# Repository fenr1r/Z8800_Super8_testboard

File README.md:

# Z8800_Super8_testboard

Test board for MCU Z08800020 (Super8 / Z8) from Zilog.

More details : plz refer my blog [https://vita-brevis.hatenablog.com/archive/category/Z8800%20%28Super8%29].

## bugs

**These bugs are currently NOT fixed yet**. Be careful for using assets.

- No need for implementing pull-up register arrays RN2. Instead of this, you HAVE TO ADD pull-down register to A13-A15
- Port 2 signals are wrongly connected to DAC08. The bits order are backwards. B0 SHOULD be connected to P2_7, B7 SHOULD be connected to P2_0.
- The pin assigns of DTR and RxD on the D-sub connector are backwards.
- GAL logic comment SHOULD BE FIXED as : #RAM_WE = #DS # R/#W, #RAM_OE = #DS # !R/#W

These are not bugs but recommended to be fixed:

- Add #DM (P3_5) signal to GAL input. #DM is a signal to distinguish between access to the program memory and to the data memory.

## Spec

- ROM 27256 (32kB)
- RAM 62256 (32kB)
- Address decoder GAL16V8B
- 1 LED port (LED x8)
- 1 DAC port (DAC08 ... to accomplish the sine wave generation described on Super8 Application Note)
- 1 UART port (RS-232)

## Assets

### Schematics

KiCad v9

[KiCad_Z8800](KiCad_Z8800/KiCad_Z8800_sch.pdf)

### PCB design

KiCad v9

### GAL JEDEC file

WinCupl

### Program

Macro Asseembler

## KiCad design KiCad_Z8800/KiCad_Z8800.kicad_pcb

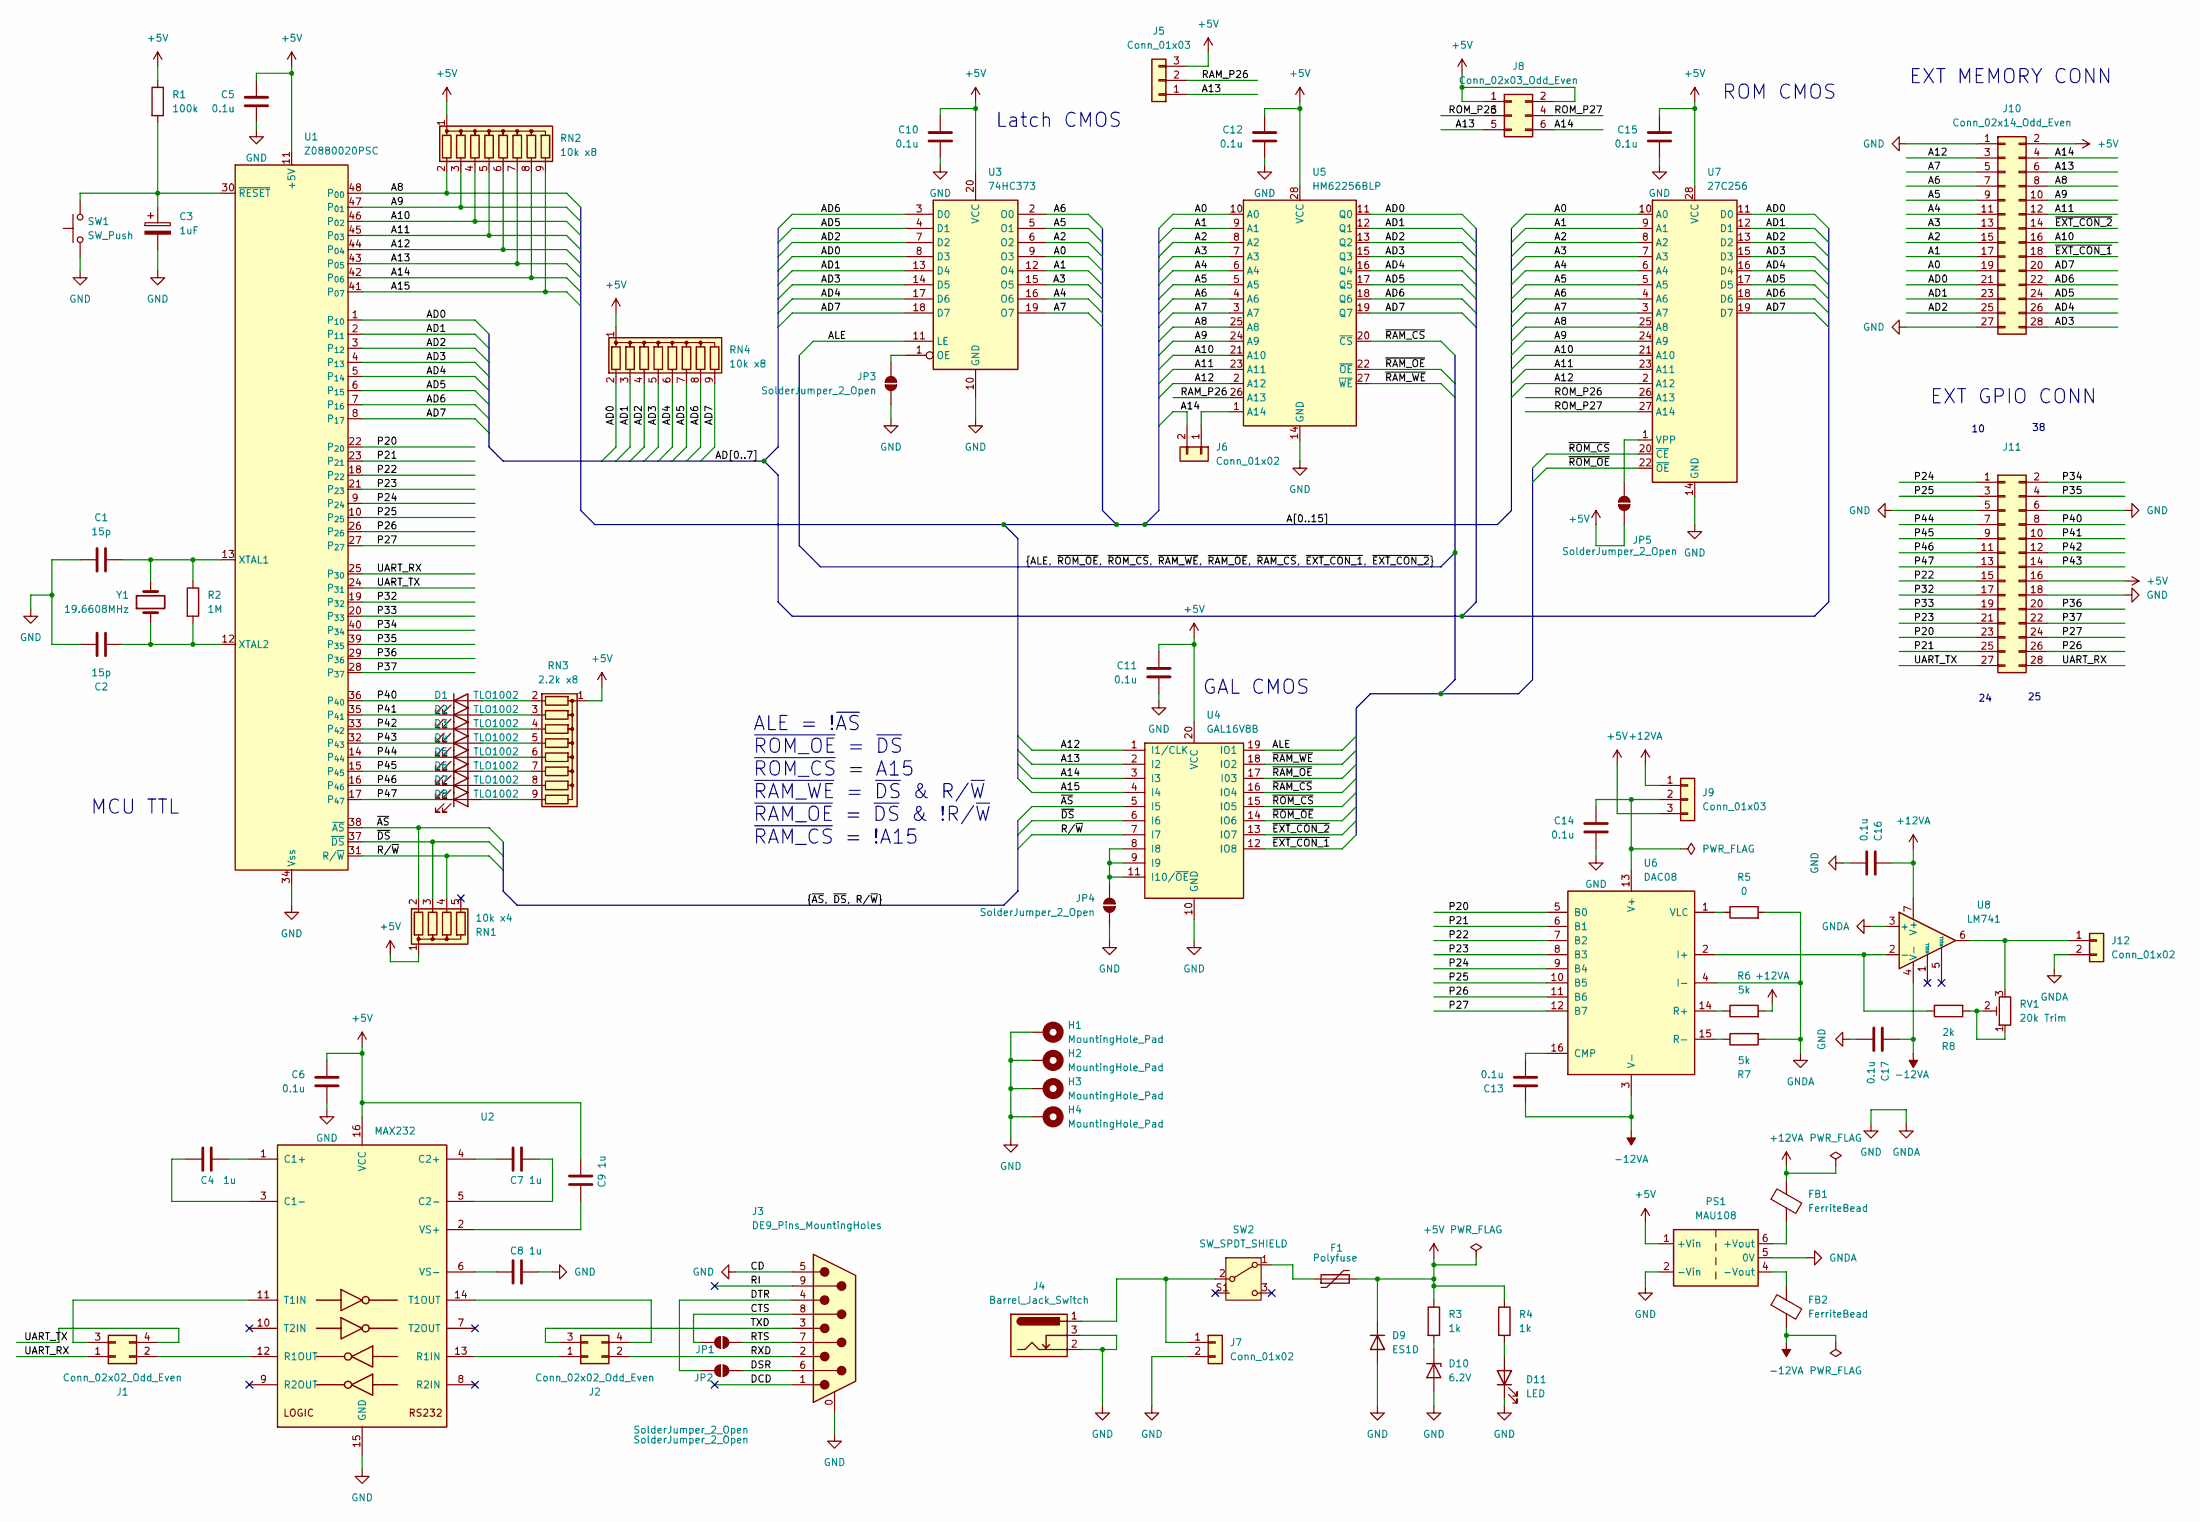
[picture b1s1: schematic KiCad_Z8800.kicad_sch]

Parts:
C1, C2: 15p; C_1206_3216Metric_Pad1.33x1.80mm_HandSolder
C3: 1uF; CP_Radial_D6.3mm_P2.50mm
C4, C7, C8, C9: 1u; C_0603_1608Metric_Pad1.08x0.95mm_HandSolder
C5, C10, C15, C16, C17: 0.1u; C_0603_1608Metric_Pad1.08x0.95mm_HandSolder
C6, C11, C12, C13, C14: 0.1u; C_Disc_D4.7mm_W2.5mm_P5.00mm
D1, D2, D3, D4, D5, D6, D7, D8: TLO1002; LED_0805_2012Metric_Pad1.15x1.40mm_HandSolder
D9: ES1D; D_SMA_Handsoldering
D10: 6.2V; D_DO-35_SOD27_P2.54mm_Vertical_KathodeUp
D11: LED; LED_D3.0mm
F1: Polyfuse; C_Disc_D8.0mm_W2.5mm_P5.00mm
FB1, FB2: FerriteBead; L_0603_1608Metric_Pad1.05x0.95mm_HandSolder
H1, H2, H3, H4: MountingHole_Pad; MountingHole_3.2mm_M3_Pad
J1, J2: Conn_02x02_Odd_Even; PinHeader_2x02_P2.54mm_Vertical
J3: DE9_Pins_MountingHoles; DSUB-9_Pins_Horizontal_P2.77x2.84mm_EdgePinOffset4.94mm_Hou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
J4: Barrel_Jack_Switch; BarrelJack_Horizontal
J5, J9: Conn_01x03; PinHeader_1x03_P2.54mm_Vertical
J6: Conn_01x02; PinHeader_1x02_P2.54mm_Vertical
J7, J12: Conn_01x02; JST_XH_B2B-XH-A_1x02_P2.50mm_Vertical
J8: Conn_02x03_Odd_Even; PinHeader_2x03_P2.54mm_Vertical
J10, J11: Conn_02x14_Odd_Even; PinHeader_2x14_P2.54mm_Vertical
JP1, JP2, JP3, JP4, JP5: SolderJumper_2_Open; SolderJumper-2_P1.3mm_Open_RoundedPad1.0x1.5mm
PS1: MAU108; Converter_DCDC_XP_POWER-IAxxxxS_THT
R1: 100k; R_Axial_DIN0207_L6.3mm_D2.5mm_P7.62mm_Horizontal
R2: 1M; R_0603_1608Metric_Pad0.98x0.95mm_HandSolder
R3, R4: 1k; R_Axial_DIN0207_L6.3mm_D2.5mm_P7.62mm_Horizontal
R5: 0; R_0603_1608Metric_Pad0.98x0.95mm_HandSolder
R6, R7: 5k; R_Axial_DIN0207_L6.3mm_D2.5mm_P7.62mm_Horizontal
R8: 2k; R_Axial_DIN0207_L6.3mm_D2.5mm_P7.62mm_Horizontal
RN1: 10k x4; R_Array_SIP5
RN2, RN4: 10k x8; R_Array_SIP9
RN3: 2.2k x8; R_Array_SIP9
RV1: 20k Trim; Potentiometer_Runtron_RM-065_Vertical
SW1: SW_Push; SW_PUSH_6mm
SW2: SW_SPDT_SHIELD; SW_2MS1-T1-B4-VS2-Q-E-S
U1: Z0880020PSC; DIP-48_W15.24mm_Socket_LongPads
U2: MAX232; DIP-16_W7.62mm_Socket_LongPads
U3: 74HC373; DIP-20_W7.62mm_Socket_LongPads
U4: GAL16V8B; DIP-20_W7.62mm_Socket_LongPads
U5: HM62256BLP; DIP-28_W15.24mm
U6: DAC08; DIP-16_W7.62mm_Socket_LongPads
U7: 27C256; DIP_Socket-28_W11.9mm_W12.7mm_W15.24mm_W17.78mm_W18.5mm_3M_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
U8: LM741; DIP-8_W7.62mm_Socket_LongPads
Y1: 19.6608MHz; Crystal_HC49-U_Vertical

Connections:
+5V: C5.1, C6.1, C9.1, C10.1, C11.1, C12.1, C15.1, D9.1 (K), F1.2, J5.3, J8.1, J8.2, J9.3, J10.2, J11.16, JP5.2 (B), PS1.1 (+Vin), R1.1, R3.1, R4.1, RN1.1 (common), RN2.1 (common), RN3.1 (common), RN4.1 (common), U1.11 (+5V), U2.16 (VCC), U3.20 (VCC), U4.20 (VCC), U5.28 (VCC), U7.28 (VCC)
+12VA: C16.1, FB1.1, J9.1, R6.2, U8.7 (V+)
-12VA: C13.1, C17.1, FB2.2, U6.3 (V-), U8.4 (V-)
/A0: J10.19, U3.9 (O3), U5.10 (A0), U7.10 (A0)
/A1: J10.17, U3.12 (O4), U5.9 (A1), U7.9 (A1)
/A2: J10.15, U3.6 (O2), U5.8 (A2), U7.8 (A2)
/A3: J10.13, U3.15 (O5), U5.7 (A3), U7.7 (A3)
/A4: J10.11, U3.16 (O6), U5.6 (A4), U7.6 (A4)
/A5: J10.9, U3.5 (O1), U5.5 (A5), U7.5 (A5)
/A6: J10.7, U3.2 (O0), U5.4 (A6), U7.4 (A6)
/A7: J10.5, U3.19 (O7), U5.3 (A7), U7.3 (A7)
/A8: J10.8, RN2.2 (R1), U1.48 (P_{00}), U5.25 (A8), U7.25 (A8)
/A9: J10.10, RN2.3 (R2), U1.47 (P_{01}), U5.24 (A9), U7.24 (A9)
/A10: J10.16, RN2.4 (R3), U1.46 (P_{02}), U5.21 (A10), U7.21 (A10)
/A11: J10.12, RN2.5 (R4), U1.45 (P_{03}), U5.23 (A11), U7.23 (A11)
/A12: J10.3, RN2.6 (R5), U1.44 (P_{04}), U4.1 (I1/CLK), U5.2 (A12), U7.2 (A12)
/A13: J5.1, J8.5, J10.6, RN2.7 (R6), U1.43 (P_{05}), U4.2 (I2)
/A14: J6.2, J8.6, J10.4, RN2.8 (R7), U1.42 (P_{06}), U4.3 (I3)
/A15: RN2.9 (R8), U1.41 (P_{07}), U4.4 (I4)
/AD0: J10.21, RN4.2 (R1), U1.1 (P_{10}), U3.8 (D3), U5.11 (Q0), U7.11 (D0)
/AD1: J10.23, RN4.3 (R2), U1.2 (P_{11}), U3.13 (D4), U5.12 (Q1), U7.12 (D1)
/AD2: J10.25, RN4.4 (R3), U1.3 (P_{12}), U3.7 (D2), U5.13 (Q2), U7.13 (D2)
/AD3: J10.28, RN4.5 (R4), U1.4 (P_{13}), U3.14 (D5), U5.15 (Q3), U7.15 (D3)
/AD4: J10.26, RN4.6 (R5), U1.5 (P_{14}), U3.17 (D6), U5.16 (Q4), U7.16 (D4)
/AD5: J10.24, RN4.7 (R6), U1.6 (P_{15}), U3.4 (D1), U5.17 (Q5), U7.17 (D5)
/AD6: J10.22, RN4.8 (R7), U1.7 (P_{16}), U3.3 (D0), U5.18 (Q6), U7.18 (D6)
/AD7: J10.20, RN4.9 (R8), U1.8 (P_{17}), U3.18 (D7), U5.19 (Q7), U7.19 (D7)
/ALE: U3.11 (LE), U4.19 (IO1)
/CTS: J3.8, JP1.2 (B)
/DCD: J3.1
/DSR: J3.6, JP2.1 (A)
/DTR: J3.4, JP2.2 (B)
/P20: J11.23, U1.22 (P_{20}), U6.5 (B0)
/P21: J11.25, U1.23 (P_{21}), U6.6 (B1)
/P22: J11.15, U1.18 (P_{22}), U6.7 (B2)
/P23: J11.21, U1.21 (P_{23}), U6.8 (B3)
/P24: J11.1, U1.9 (P_{24}), U6.9 (B4)
/P25: J11.3, U1.10 (P_{25}), U6.10 (B5)
/P26: J11.26, U1.26 (P_{26}), U6.11 (B6)
/P27: J11.24, U1.27 (P_{27}), U6.12 (B7)
/P32: J11.17, U1.19 (P_{32})
/P33: J11.19, U1.20 (P_{33})
/P34: J11.2, U1.40 (P_{34})
/P35: J11.4, U1.39 (P_{35})
/P36: J11.20, U1.29 (P_{36})
/P37: J11.22, U1.28 (P_{37})
/P40: D1.1 (K), J11.8, U1.36 (P_{40})
/P41: D2.1 (K), J11.10, U1.35 (P_{41})
/P42: D3.1 (K), J11.12, U1.33 (P_{42})
/P43: D4.1 (K), J11.14, U1.32 (P_{43})
/P44: D5.1 (K), J11.7, U1.14 (P_{44})
/P45: D6.1 (K), J11.9, U1.15 (P_{45})
/P46: D7.1 (K), J11.11, U1.16 (P_{46})
/P47: D8.1 (K), J11.13, U1.17 (P_{47})
/RAM_P26: J5.2, U5.26 (A13)
/RI: J3.9
/ROM_P26: J8.3, U7.26 (A13)
/ROM_P27: J8.4, U7.27 (A14)
/RTS: J3.7, JP1.1 (A)
/RXD: J2.2, J3.2
/R/~W: RN1.4 (R3), U1.31 (R/~W), U4.7 (I7)
/TXD: J2.3, J3.3
/UART_RX: J1.1, J11.28, U1.25 (P_{30})
/UART_TX: J1.4, J11.27, U1.24 (P_{31})
/~AS: RN1.2 (R1), U1.38 (~AS), U4.5 (I5)
/~DS: RN1.3 (R2), U1.37 (~DS), U4.6 (I6)
/~EXT_CON_1: J10.18, U4.12 (IO8)
/~EXT_CON_2: J10.14, U4.13 (IO7)
/~RAM_CS: U4.16 (IO4), U5.20 (~CS)
/~RAM_OE: U4.17 (I03), U5.22 (~OE)
/~RAM_WE: U4.18 (IO2), U5.27 (~WE)
/~ROM_CS: U4.15 (IO5), U7.20 (~CE)
/~ROM_OE: U4.14 (IO6), U7.22 (~OE)
GND: C1.1, C2.1, C3.2, C5.2, C6.2, C8.1, C10.2, C11.2, C12.2, C14.2, C15.2, C16.2, C17.2, D9.2 (A), D10.2 (A), D11.1 (K), H1.1, H2.1, H3.1, H4.1, J3.0 (PAD), J3.5, J4.2, J4.3, J7.2, J10.1, J10.27, J11.5, J11.6, J11.18, J12.2, JP3.1 (A), JP4.1 (A), PS1.2 (-Vin), PS1.5 (0V), R5.2, R7.2, SW1.1, U1.34 (Vss), U2.15 (GND), U3.10 (GND), U4.10 (GND), U5.14 (GND), U6.4 (I-), U7.14 (GND), U8.3 (+)
unnamed: D1.2 (A), RN3.2 (R1)
unnamed: D2.2 (A), RN3.3 (R2)
unnamed: D3.2 (A), RN3.4 (R3)
unnamed: D4.2 (A), RN3.5 (R4)
unnamed: D5.2 (A), RN3.6 (R5)
unnamed: D6.2 (A), RN3.7 (R6)
unnamed: D7.2 (A), RN3.8 (R7)
unnamed: D8.2 (A), RN3.9 (R8)
unnamed: D10.1 (K), R3.2
unnamed: D11.2 (A), R4.2
unnamed: J1.2, U2.12 (R1OUT)
unnamed: J1.3, U2.11 (T1IN)
unnamed: J2.1, U2.13 (R1IN)
unnamed: J2.4, U2.14 (T1OUT)
unnamed: J6.1, U5.1 (A14)
unnamed: J4.1, J7.1, SW2.2 (B)
unnamed: C14.1, J9.2, U6.13 (V+)
unnamed: J12.1, RV1.3, U8.6
unnamed: JP3.2 (B), U3.1 (OE)
unnamed: JP4.2 (B), U4.8 (I8), U4.9 (I9), U4.11 (I10/~OE)
unnamed: JP5.1 (A), U7.1 (VPP)
unnamed: FB1.2, PS1.6 (+Vout)
unnamed: FB2.1, PS1.4 (-Vout)
unnamed: R8.2, RV1.1, RV1.2
unnamed: F1.1, SW2.1 (A)
unnamed: C1.2, R2.1, U1.13 (XTAL1), Y1.2
unnamed: C2.2, R2.2, U1.12 (XTAL2), Y1.1
unnamed: C3.1, R1.2, SW1.2, U1.30 (~RESET)
unnamed: C4.2, U2.1 (C1+)
unnamed: C4.1, U2.3 (C1-)
unnamed: C7.2, U2.4 (C2+)
unnamed: C7.1, U2.5 (C2-)
unnamed: C9.2, U2.2 (VS+)
unnamed: C8.2, U2.6 (VS-)
unnamed: C13.2, U6.16 (CMP)
unnamed: R8.1, U6.2 (I+), U8.2 (-)
unnamed: R6.1, U6.14 (R+)
unnamed: R7.1, U6.15 (R-)
unnamed: R5.1, U6.1 (VLC)

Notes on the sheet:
GAL CMOS
EXT GPIO CONN
Latch CMOS
ALE = !~{AS} ~{ROM_OE} = ~{DS} ~{ROM_CS} = A15 ~{RAM_WE} = ~{DS} & R/~{W} ~{RAM_OE} = ~{DS} & !R/~{W} ~{RAM_CS} = !A15
ROM CMOS
MCU TTL
EXT MEMORY CONN

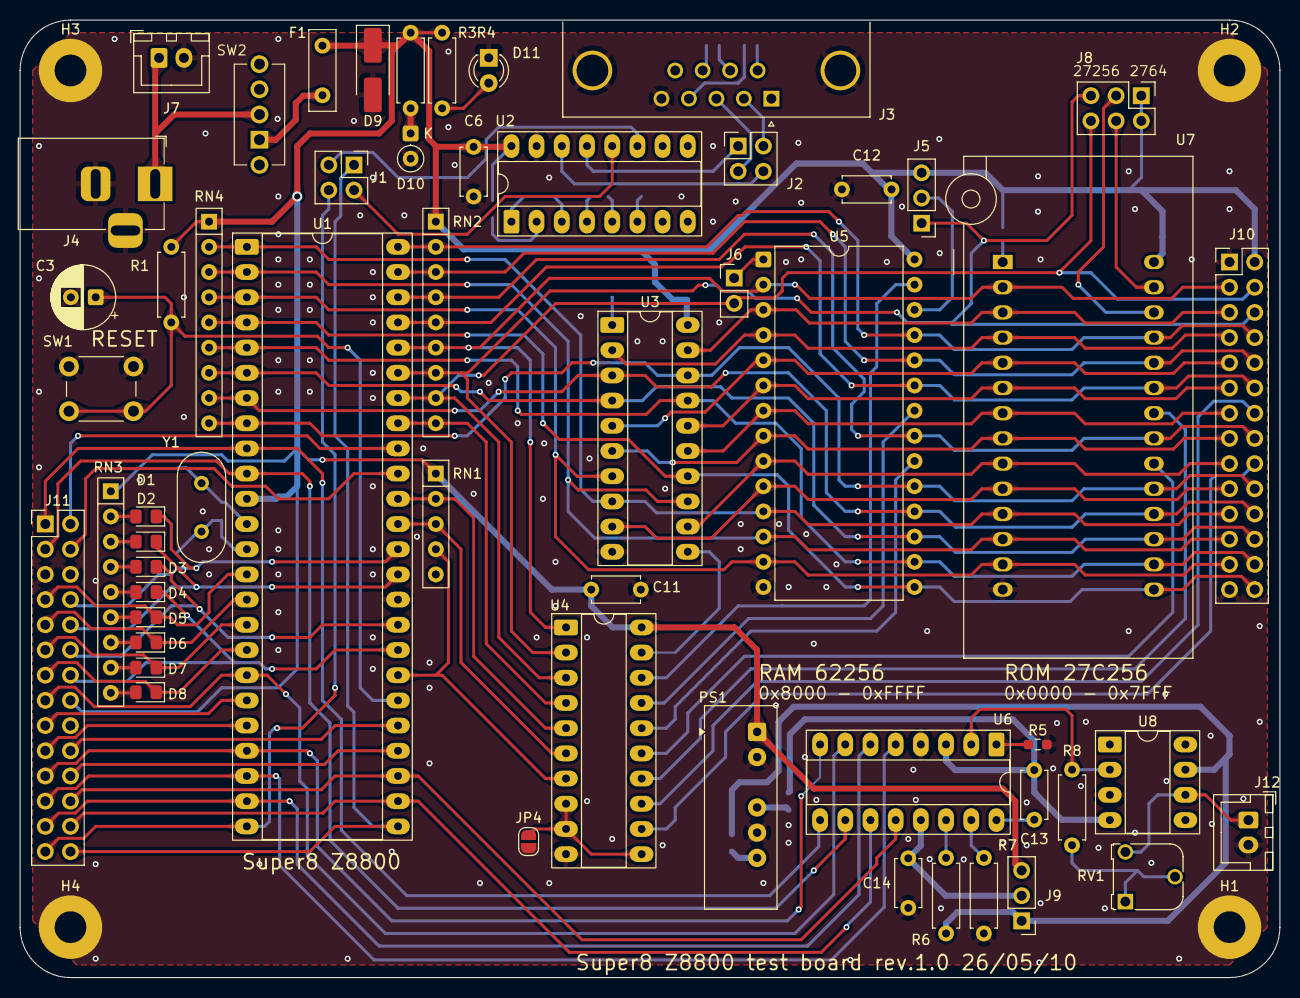
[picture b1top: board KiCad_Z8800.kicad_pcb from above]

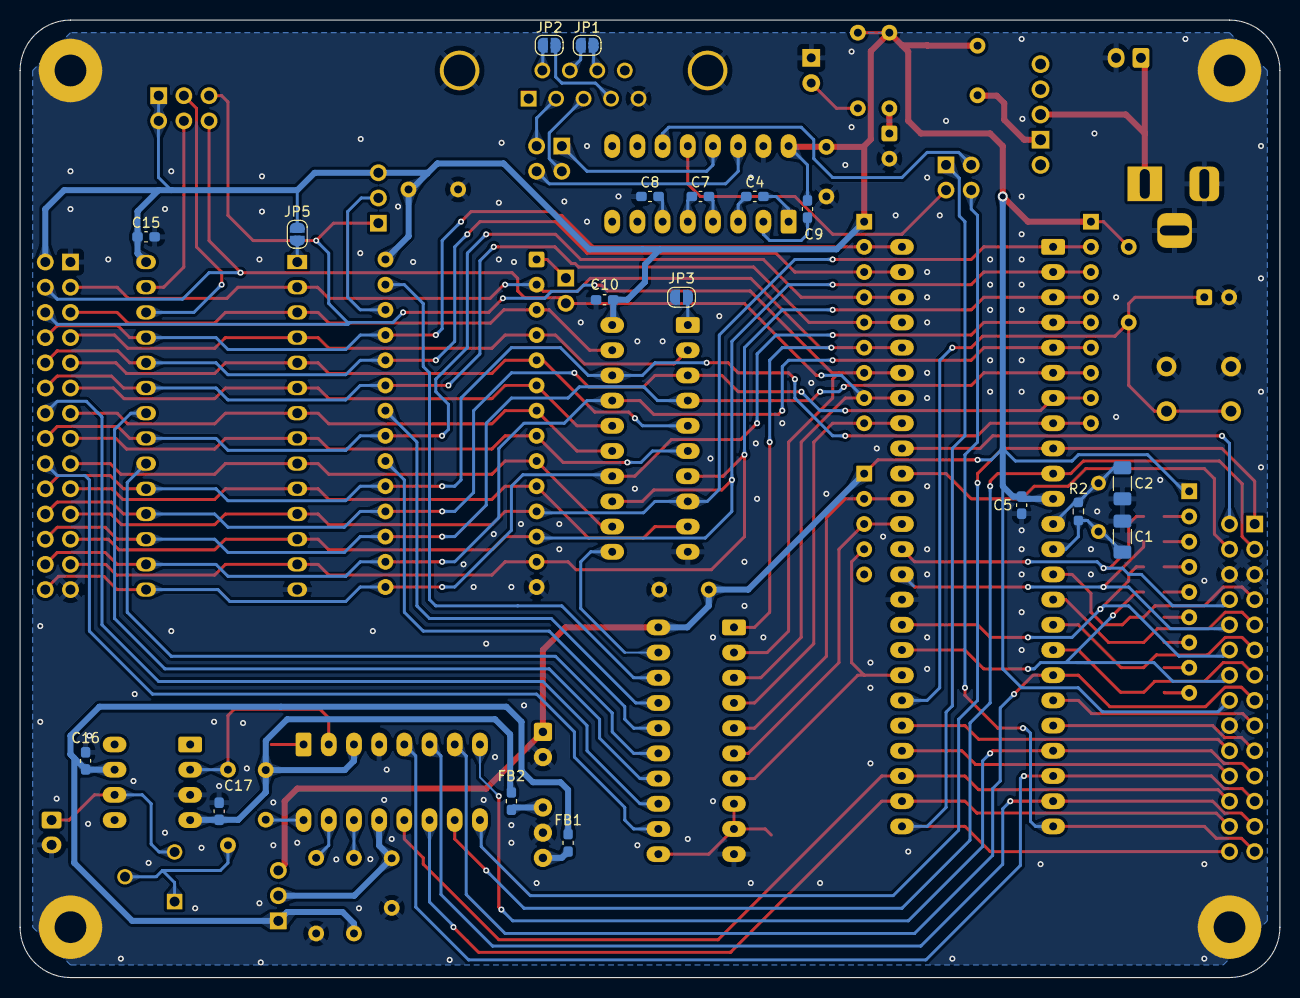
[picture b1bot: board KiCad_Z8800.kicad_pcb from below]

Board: 2 copper layers, 127.0 x 96.5 mm, 77 parts (18 on the bottom side), 111 nets.

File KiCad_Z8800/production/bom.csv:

Designator,Footprint,Quantity,Value,LCSC Part #
"C1, C2",1206,2,15p,
"C10, C15, C16, C17, C5",0603,5,0.1u,
"C11, C12, C13, C14, C6",C_Disc_D4.7mm_W2.5mm_P5.00mm,5,0.1u,
C3,CP_Radial_D6.3mm_P2.50mm,1,1uF,
"C4, C7, C8, C9",0603,4,1u,
"D1, D2, D3, D4, D5, D6, D7, D8",0805,8,TLO1002,
D10,D_DO-35_SOD27_P2.54mm_Vertical_KathodeUp,1,6.2V,
D11,LED_D3.0mm,1,LED,
D9,D_SMA_Handsoldering,1,D,
F1,C_Disc_D8.0mm_W2.5mm_P5.00mm,1,Polyfuse,
"FB1, FB2",0603,2,FerriteBead,
"J1, J2",PinHeader_2x02_P2.54mm_Vertical,2,Conn_02x02_Odd_Even,
"J10, J11",PinHeader_2x14_P2.54mm_Vertical,2,Conn_02x14_Odd_Even,
"J12, J7",JST_XH_B2B-XH-A_1x02_P2.50mm_Vertical,2,Conn_01x02,
J3,DSUB-9_Pins_Horizontal_P2.77x2.84mm_EdgePinOffset4.94mm_Housed_MountingHolesOffset4.94mm,1,DE9_Pins_MountingHoles,
J4,BarrelJack_Horizontal,1,Barrel_Jack_Switch,
"J5, J9",PinHeader_1x03_P2.54mm_Vertical,2,Conn_01x03,
J6,PinHeader_1x02_P2.54mm_Vertical,1,Conn_01x02,
J8,PinHeader_2x03_P2.54mm_Vertical,1,Conn_02x03_Odd_Even,
PS1,Converter_DCDC_XP_POWER-IAxxxxS_THT,1,MAU108,
R1,R_Axial_DIN0207_L6.3mm_D2.5mm_P7.62mm_Horizontal,1,100k,
R2,0603,1,1M,
"R3, R4",R_Axial_DIN0207_L6.3mm_D2.5mm_P7.62mm_Horizontal,2,1k,
R5,0603,1,0,
"R6, R7",R_Axial_DIN0207_L6.3mm_D2.5mm_P7.62mm_Horizontal,2,5k,
R8,R_Axial_DIN0207_L6.3mm_D2.5mm_P7.62mm_Horizontal,1,2k,
RN1,R_Array_SIP5,1,10k x4,
"RN2, RN4",R_Array_SIP9,2,10k x8,
RN3,R_Array_SIP9,1,2.2k x8,
RV1,Potentiometer_Runtron_RM-065_Vertical,1,20k Trim,
SW1,SW_PUSH_6mm,1,SW_Push,
SW2,SW_2MS1-T1-B4-VS2-Q-E-S,1,SW_SPDT_SHIELD,
U1,DIP-48_W15.24mm_Socket_LongPads,1,Z0880020PSC,
U2,DIP-16_W7.62mm_Socket_LongPads,1,MAX232,
U3,DIP-20_W7.62mm_Socket_LongPads,1,74HC373,
U4,DIP-20_W7.62mm_Socket_LongPads,1,GAL16V8B,
U5,DIP-28_W15.24mm,1,HM62256BLP,
U6,DIP-16_W7.62mm_Socket_LongPads,1,DAC08,
U7,DIP_Socket-28_W11.9mm_W12.7mm_W15.24mm_W17.78mm_W18.5mm_3M_228-1277-00-0602J,1,27C256,
U8,DIP-8_W7.62mm_Socket_LongPads,1,LM741,
Y1,Crystal_HC49-U_Vertical,1,19.6608MHz,
